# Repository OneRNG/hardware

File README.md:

hardware
========

Hardware designs for OneRNG - Eagle files - 2 layers

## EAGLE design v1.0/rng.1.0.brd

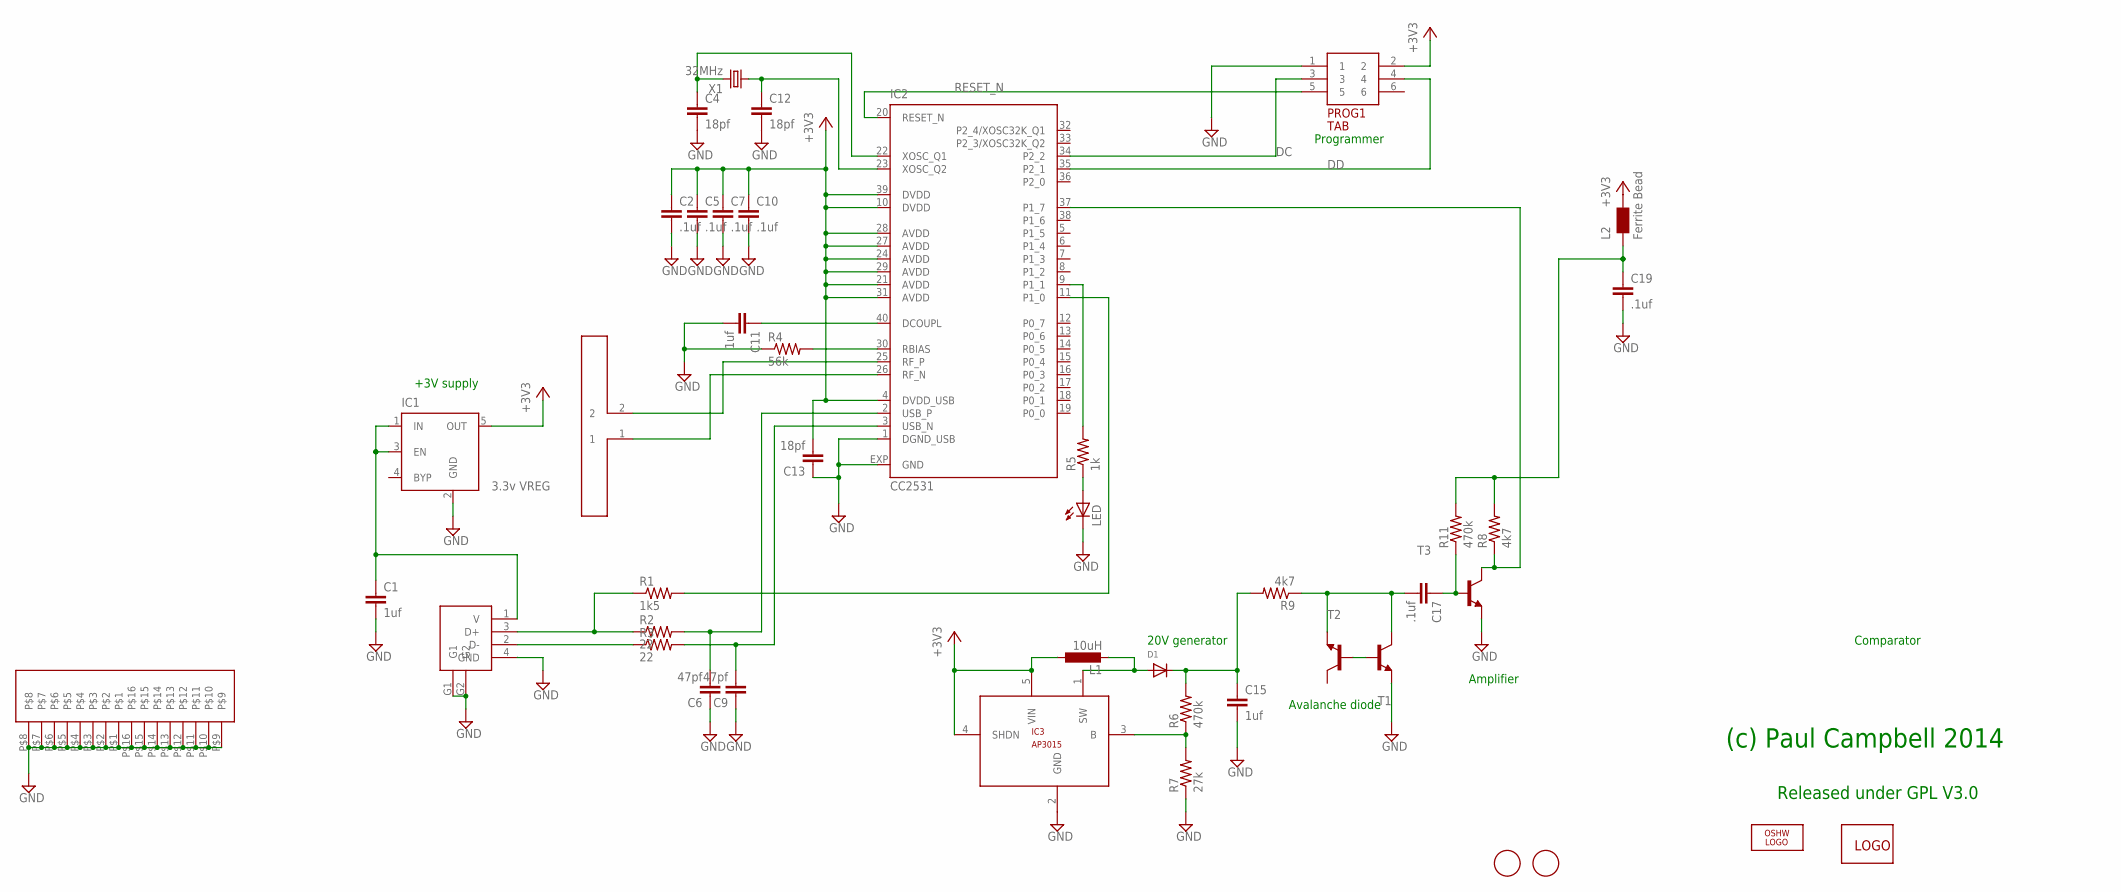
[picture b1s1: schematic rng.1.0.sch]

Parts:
C1, C11, C15: 1uf; C0603
C2, C7, C10, C17, C19: .1uf; C0603
C4, C12, C13: 18pf; C0603
C5: .1uf; C0603K
C6, C9: 47pf; C0603
D1: DIODESOD-323F; SOD-323F
IC1: 3.3v VREG; SOT23-5
IC2: CC2531; RHA_S-PVQFN-N40
IC3: AP3015; SOT23-5
L1: 10uH; L2012C
L2: Ferrite Bead; 0805
LED: LEDCHIP-LED0603; CHIP-LED0603
LOGO1: OSHW_LOGO_FILLX0100-NT; OSHW_FILLX100_NOTEXT
PROG1: TAB; TAG
R1: 1k5; R0603
R2, R3: 22; R0603
R4: 56k; R0603
R5: 1k; R0603
R6, R11: 470k; R0603
R7: 27k; R0603
R8, R9: 4k7; R0603
T1, T2, T3: BCF32-NPN-SOT23-BEC; SOT23-BEC
U$1: USB-RAW; USBY
U$2: DIPOLEDIPOLE1; DIPOLE
U$3, U$4: FIDUCIAL; FIDUCIAL_1MM
U$5: MOONBASE-LOGO
U$6: BMI-S-2-09; SHIELD-209
X1: 32MHz; SM49

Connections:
+3V3: C2.1, C5.1, C7.1, C10.1, C13.2, IC1.5 (OUT), IC2.4 (DVDD_USB), IC2.10 (DVDD), IC2.21 (AVDD), IC2.24 (AVDD), IC2.27 (AVDD), IC2.28 (AVDD), IC2.29 (AVDD), IC2.31 (AVDD), IC2.39 (DVDD), IC3.4 (SHDN), IC3.5 (VIN), L1.1, L2.2, PROG1.2
DC: IC2.34 (P2_2), PROG1.3
DD: IC2.35 (P2_1), PROG1.4
GND: C1.2, C2.2, C4.2, C5.2, C6.1, C7.2, C9.1, C10.2, C11.2, C12.2, C13.1, C15.2, C19.2, IC1.2 (GND), IC2.1 (DGND_USB), IC2.EXP (GND), IC3.2 (GND), LED.C, PROG1.1, R4.1, R7.1, T2.E, T3.E, U$1.4 (GND), U$1.G1, U$1.G2, U$6.P$1, U$6.P$2, U$6.P$3, U$6.P$4, U$6.P$5, U$6.P$6, U$6.P$7, U$6.P$8, U$6.P$9, U$6.P$10, U$6.P$11, U$6.P$12, U$6.P$13, U$6.P$14, U$6.P$15, U$6.P$16
unnamed: T1.B, T2.B
unnamed: C1.1, IC1.1 (IN), IC1.3 (EN), U$1.1 (V)
unnamed: C6.2, IC2.2 (USB_P), R2.2
unnamed: R3.1, U$1.2 (D-)
unnamed: C9.2, IC2.3 (USB_N), R3.2
unnamed: LED.A, R5.1
unnamed: R1.1, R2.1, U$1.3 (D+)
unnamed: IC2.11 (P1_0), R1.2
unnamed: IC2.9 (P1_1), R5.2
unnamed: C11.1, IC2.40 (DCOUPL)
unnamed: IC2.37 (P1_7), R8.1, T3.C
unnamed: C17.2, R9.1, T1.E, T2.C
unnamed: C17.1, R11.1, T3.B
unnamed: C15.1, D1.C, R6.2, R9.2
unnamed: C4.1, IC2.22 (XOSC_Q1), X1.2
unnamed: C12.1, IC2.23 (XOSC_Q2), X1.1
unnamed: C19.1, L2.1, R8.2, R11.2
unnamed: IC2.30 (RBIAS), R4.2
unnamed: IC2.25 (RF_P), U$2.2
unnamed: IC2.26 (RF_N), U$2.1
unnamed: D1.A, IC3.1 (SW), L1.2
R88: IC3.3 (B), R6.1, R7.2
RESET_N: IC2.20 (RESET_N), PROG1.5

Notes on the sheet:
(c) Paul Campbell 2014
Avalanche diode
Amplifier
Programmer
20V generator
+3V supply
Comparator
Released under GPL V3.0

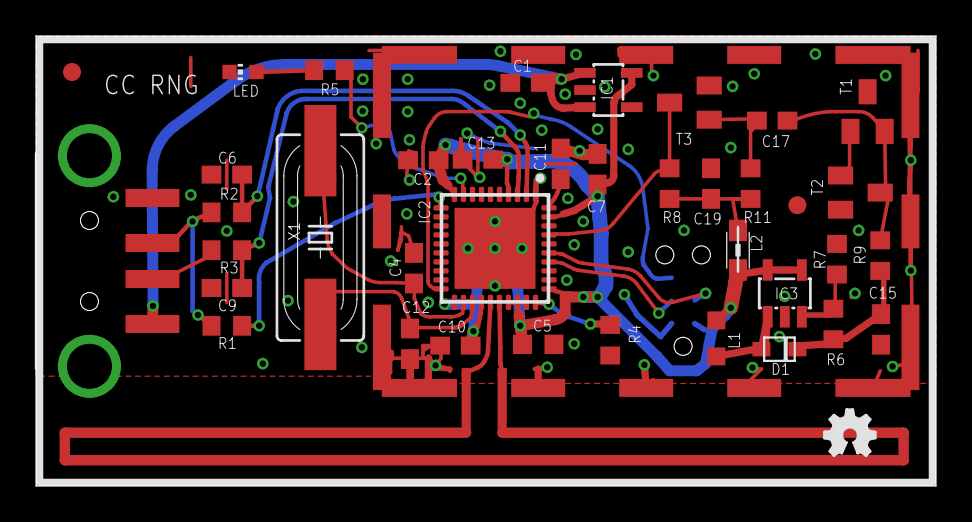
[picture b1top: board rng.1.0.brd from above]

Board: 2 copper layers, 50.0 x 25.0 mm, 43 parts (0 on the bottom side), 27 nets.

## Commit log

2014-12-14 first checkin version 1.0
2015-06-14 add v2.0 board designs
2017-01-30 fix typo in part number AP3105->AP3015

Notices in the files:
parts and their libraries:
wuerth-elektronik: Copyright: Würth Elektronik eiSos
